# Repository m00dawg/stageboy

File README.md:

StageBoy
========

Stage-Hardened ArduinoBoy, Balun, Noise Rejection Box all rolled into one.

Programming the StageBoy
------------------------

Pulling the Chip:

If you don't want to mess with the ISP headers, you can likely just stuff
an AVR chip which is already Arduinofied (it has the bootlodaer already -
as in you previously flashed it with the bootloader or bought an AVR 
from a place that will flash it for you) into an Uno board and upload
the code as you normally would. Then you can pull the chip and put it into
the StageBoy.

If you're not making any changes, and are reasonably confident with your 
soldering work, this should work without issue. Using the ISP headers, 
however, makes thins easier to troubleshoot.

Using the ISP Headers:

ISP headers have been used successful with EvilMadScientist's ISP Shield
(see http://shop.evilmadscientist.com/productsmenu/tinykitlist/253-ispshield)
and an Arduino Duemilanove. Wires are hooked up in a similar way to the
Arduino ISP how-to (see: http://arduino.cc/en/Tutorial/ArduinoISP) but
with a 6-pin ISP header on the other end. A standard ISP cable should
work, and would be a lot easier, but hasn't been tested.

With the ISP Shield, program the Arduino connect to the shield using the
ArduinoISP sketch available with the Ardunio IDE (under Examples). Then
connect the shield to the Arduino and the ISP cable to the StageBoy. Burning
the bootloader should be optional, but it has never been tested without. To
burn the bootloader, pick the Arduino board you are using as the programmer
in the Tools -> Board menu. Then set the Programmer to Arduino As ISP under
Tools -> Programmer. Then go to Tools -> Burn Bootloader.

Having done that, load up the StageBoy sketch, and then press SHIFT and click
on the upload icon. This uploads the code to the StageBoy instead of to the
Arduino board acting as the programmer.

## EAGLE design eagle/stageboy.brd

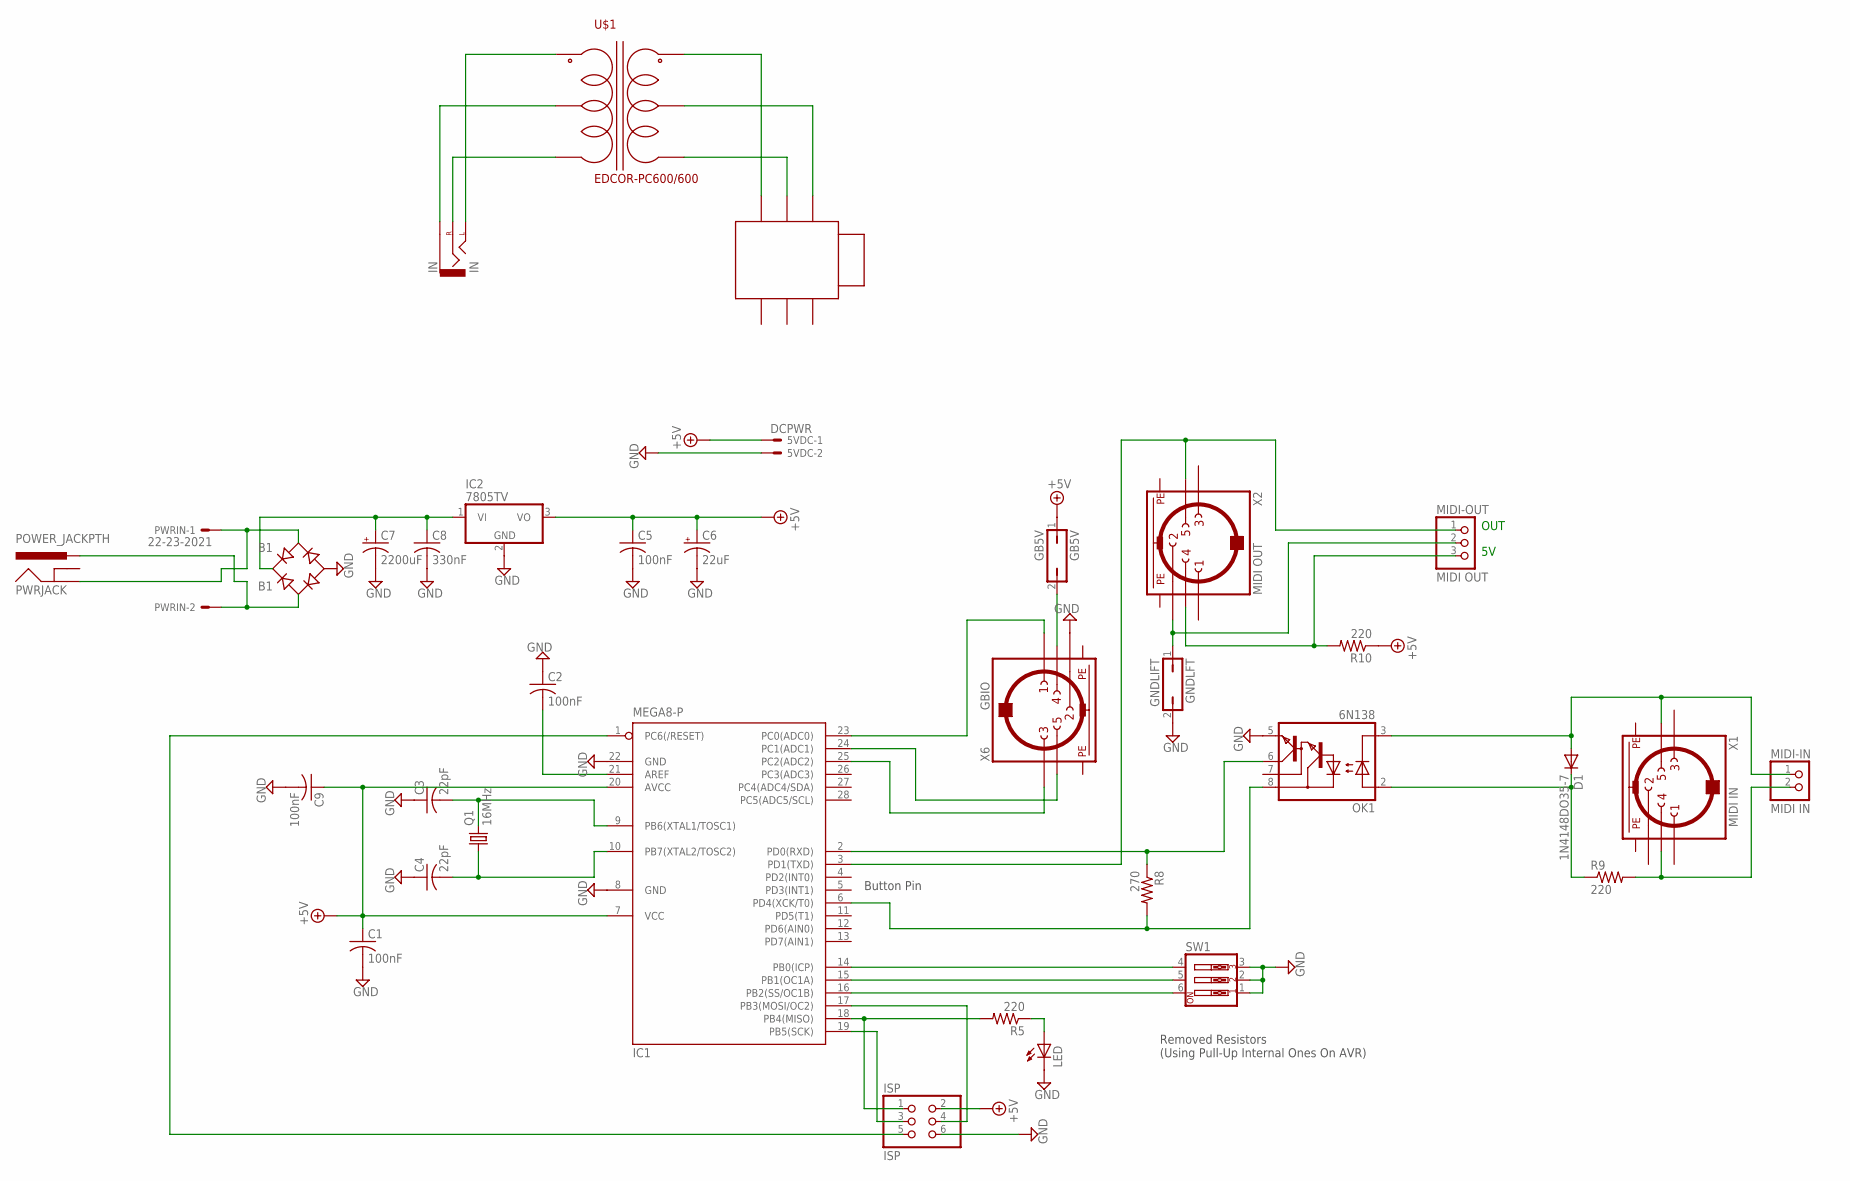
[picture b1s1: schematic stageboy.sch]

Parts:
5VDC: DCPWR; 22-23-2021
B1: B1; RB1A
C1, C2, C5, C9: 100nF; C025-025X050
C3, C4: 22pF; C025-025X050
C6: 22uF; E2,5-5
C7: 2200uF; E5-13
C8: 330nF; C025-025X050
D1: 1N4148DO35-7; DO35-7
GB5V: GB5V; JP1
GNDLFT: GNDLIFT; JP1
IC1: MEGA8-P; DIL28-3
IC2: 7805TV; TO220V
IN: IN; AUDIO-JACK
ISP: ISP; 2X03
LED: LED3MM
MIDI-IN: MIDI IN; 1X02
MIDI-OUT: MIDI OUT; 1X03
OK1: 6N138; DIL08
OUT: NMJ6HFD2
PWRIN: 22-23-2021
PWRJACK: POWER_JACKPTH; POWER_JACK_PTH
Q1: 16MHz; HC49/S
R5, R9, R10: 220; 0204/7
R8: 270; 0204/7
SW1: SW_DIP-3; EDG-03
U$1: EDCOR-PC600/600; PCW-12PIN
X1: MIDI IN; MAB5SH
X2: MIDI OUT; MAB5SH
X6: GBIO; MAB5SH

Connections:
+5V: 5VDC.1, C1.1, C5.1, C6.+, C9.1, GB5V.1, IC1.7 (VCC), IC1.20 (AVCC), IC2.3 (VO), ISP.2, R10.1
GND: 5VDC.2, B1.-, C1.2, C2.1, C3.1, C4.1, C5.2, C6.-, C7.-, C8.2, C9.2, GNDLFT.2, IC1.8 (GND), IC1.22 (GND), IC2.2 (GND), ISP.6, LED.K (C), OK1.5 (GND), SW1.1, SW1.2, SW1.3, X6.2
unnamed: IC1.1 (PC6(/RESET)), ISP.5
unnamed: C2.2, IC1.21 (AREF)
unnamed: LED.A, R5.1
unnamed: IC1.14 (PB0(ICP)), SW1.4
unnamed: IC1.15 (PB1(OC1A)), SW1.5
unnamed: IC1.16 (PB2(SS/OC1B)), SW1.6
unnamed: IC1.6 (PD4(XCK/T0)), OK1.8 (VCC), R8.2
unnamed: IC1.2 (PD0(RXD)), OK1.6 (VO), R8.1
unnamed: D1.A, MIDI-IN.1, OK1.3 (C), X1.5
unnamed: D1.C, OK1.2 (A), R9.1
unnamed: MIDI-IN.2, R9.2, X1.4
unnamed: IC1.17 (PB3(MOSI/OC2)), ISP.4
unnamed: IC1.18 (PB4(MISO)), ISP.1, R5.2
unnamed: IC1.19 (PB5(SCK)), ISP.3
unnamed: GB5V.2, X6.4
unnamed: IC1.3 (PD1(TXD)), MIDI-OUT.1, X2.5
unnamed: C4.2, IC1.10 (PB7(XTAL2/TOSC2)), Q1.1
unnamed: IC1.25 (PC2(ADC2)), X6.3
unnamed: C3.2, IC1.9 (PB6(XTAL1/TOSC1)), Q1.2
unnamed: IC1.24 (PC1(ADC1)), X6.5
unnamed: IC1.23 (PC0(ADC0)), X6.1
unnamed: MIDI-OUT.3, R10.2, X2.4
unnamed: B1.+, C7.+, C8.1, IC2.1 (VI)
unnamed: IN.TIP (LEFT), U$1.P$1
unnamed: OUT.GND-IN, U$1.P$8
unnamed: OUT.LEFT-IN, U$1.P$7
unnamed: OUT.RIGHT-IN, U$1.P$9
unnamed: IN.SLEEVE, U$1.P$2
unnamed: B1.AC2, PWRIN.1, PWRJACK.GND
unnamed: B1.AC1, PWRIN.2, PWRJACK.PWR
unnamed: IN.RING (RIGHT), U$1.P$3
unnamed: GNDLFT.1, MIDI-OUT.2, X2.2
PE: X1.PE, X1.PE@ (PE), X2.PE, X2.PE@ (PE), X6.PE, X6.PE@ (PE)

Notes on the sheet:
OUT
Button Pin
Removed Resistors (Using Pull-Up Internal Ones On AVR)

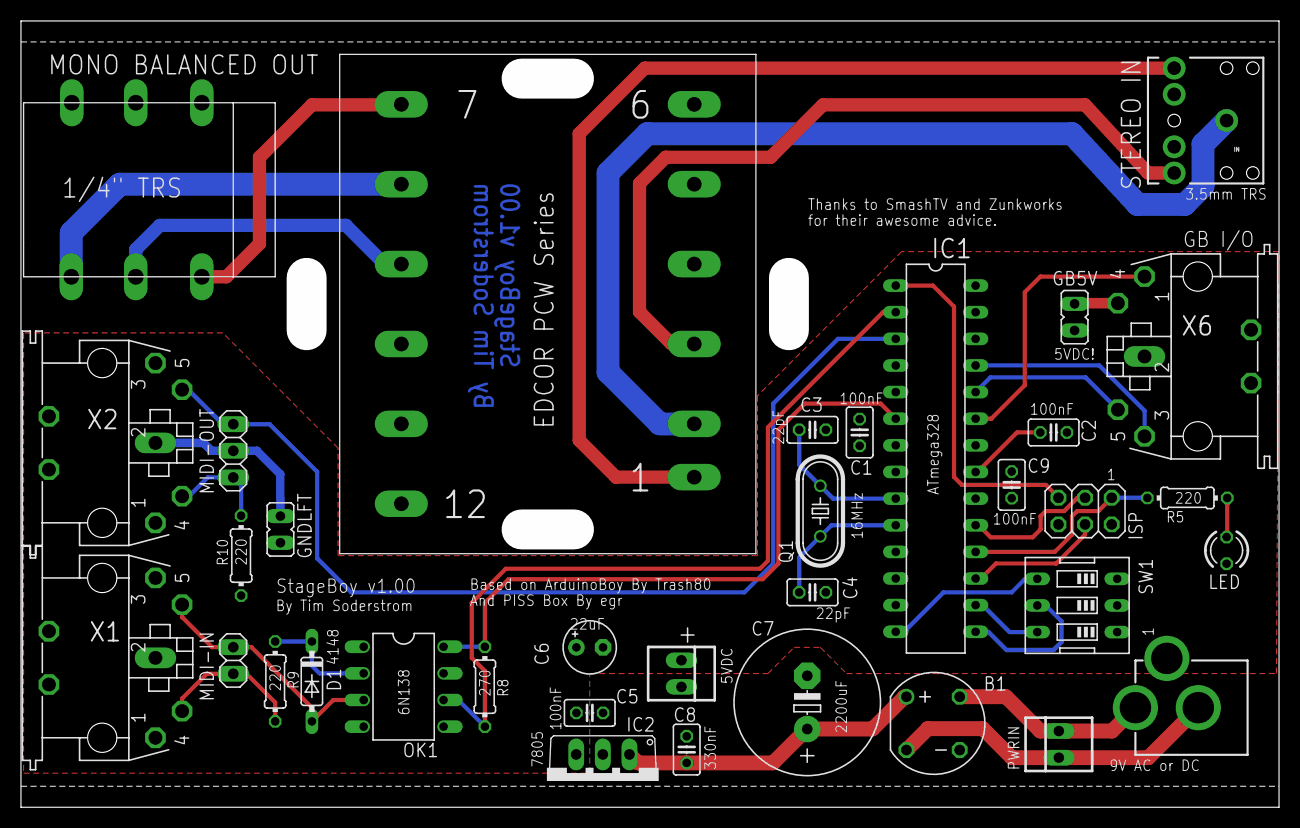
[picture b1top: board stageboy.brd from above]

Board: 2 copper layers, 116.2 x 71.2 mm, 35 parts (0 on the bottom side), 35 nets.

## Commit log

2013-08-11 Added EagleCAD layouts
2013-08-11 Imported ArduinoBoy v1.2.3
    Also began disabling routines that are no longer needed
    due to the change to using DIP switches over button/LEDs
2013-08-12 Layout Optimizations
    Moved the TRS jack towards the edge more.
    Adjusted positions on audio-in, GB in, and LEDs.
2013-08-12 Added 5VDC Header
2013-08-16 Added side panels, minor layout changes to board
2013-08-16 Added GPLv3 license file
2013-08-16 Added silkscreen and made minor formatting changes
2013-08-17 Updated panels, board layout
    Updated panels and boards to match each other and make sure things look
    decent. Also formatting things for OshPark.
2013-08-19 Swapped out DC jack
    Swapped DC jack out for one that uses large vias, as OshPark
    doesn't do plated cutouts. Looks like most any DC jack will do,
    but the part swapped was one from the SparkFun library.
2013-08-19 Moved I/O components to the edges
2013-08-19 Added an alternate board layout
    This layout moves the AVR down further away from the analog
    bits and expands the ground and power planes, while also
    replacing the pull-down resistors with the internal AVR
    pull-ups.
2013-08-19 Routing optimizations
    Made some routing optimizations in the analog section.
    Bigger traces and more direct routing.
2013-08-19 Added holes for zip-ties
    Added holes to run zipties through for the tranny.
    Thought I already added these?
2013-08-19 Fixed slant in power plane
2013-08-20 Layout Changes
    Extended PWR/GND planes
    Moved the DIP switch around
    Push the DC jack inwards to be flush-mounted to PCB
    Other minor routing changes
2013-08-20 Routing optimizations, Zip-Tie holes
    Numerous routing changes / optimizations were made to help make the
    best use of the ground and power planes for both power/gnd delivery
    as well as isolation. On that note, the isolation on both planes
    was lowered to 12 mil.
    Added two more zip-tie holes. The cuts were not showing up on
    the OshPark previews so I switched to using a line, which does show
2013-08-20 Rouge via...
2013-08-22 Picked a board layout and named it accordingly
2013-08-22 Resized the electrolytic capacitors
    The 2200uF cap was way too small, with the 22uF being only slightly
    so. Both were changed and components shifted around as needed.
2013-08-22 Minor routing change
2013-08-22 Moved the DIP switch around a bit
2013-08-22 Added Bill of Materials
2013-08-22 More minor routing changes
2013-08-22 MIDI-IN header was a bit tight
2013-09-03 Modified StageBoy Switch/LED Behavior
    Commented-out and modified the old functions for handling the
    LEDs and button and replaced them with a simple function to
    read the DIP switch and, if it's different from the current
    mode, switch to that mode.
2013-09-04 IT'S ALIVE!!!!
2013-09-09 Renamed panels for clarity
2014-06-29 Updated README with ISP information
    Updated the README with a quick and dirty howto on how to program an
    AVR while housed inside the StageBoy using ISP headers and an Arduino
    as an ISP programmer.
2014-06-29 Added a brute-force method of uploading the code.
2014-06-29 Added RestructuredText readme
2014-06-29 Removed the old Markdown README
2014-06-29 Added an explanation about the audio circuit

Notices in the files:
parts and their libraries:
SparkFun: Licensing: CC v3.0 Share-Alike You are welcome to use this library for commercial purposes.
